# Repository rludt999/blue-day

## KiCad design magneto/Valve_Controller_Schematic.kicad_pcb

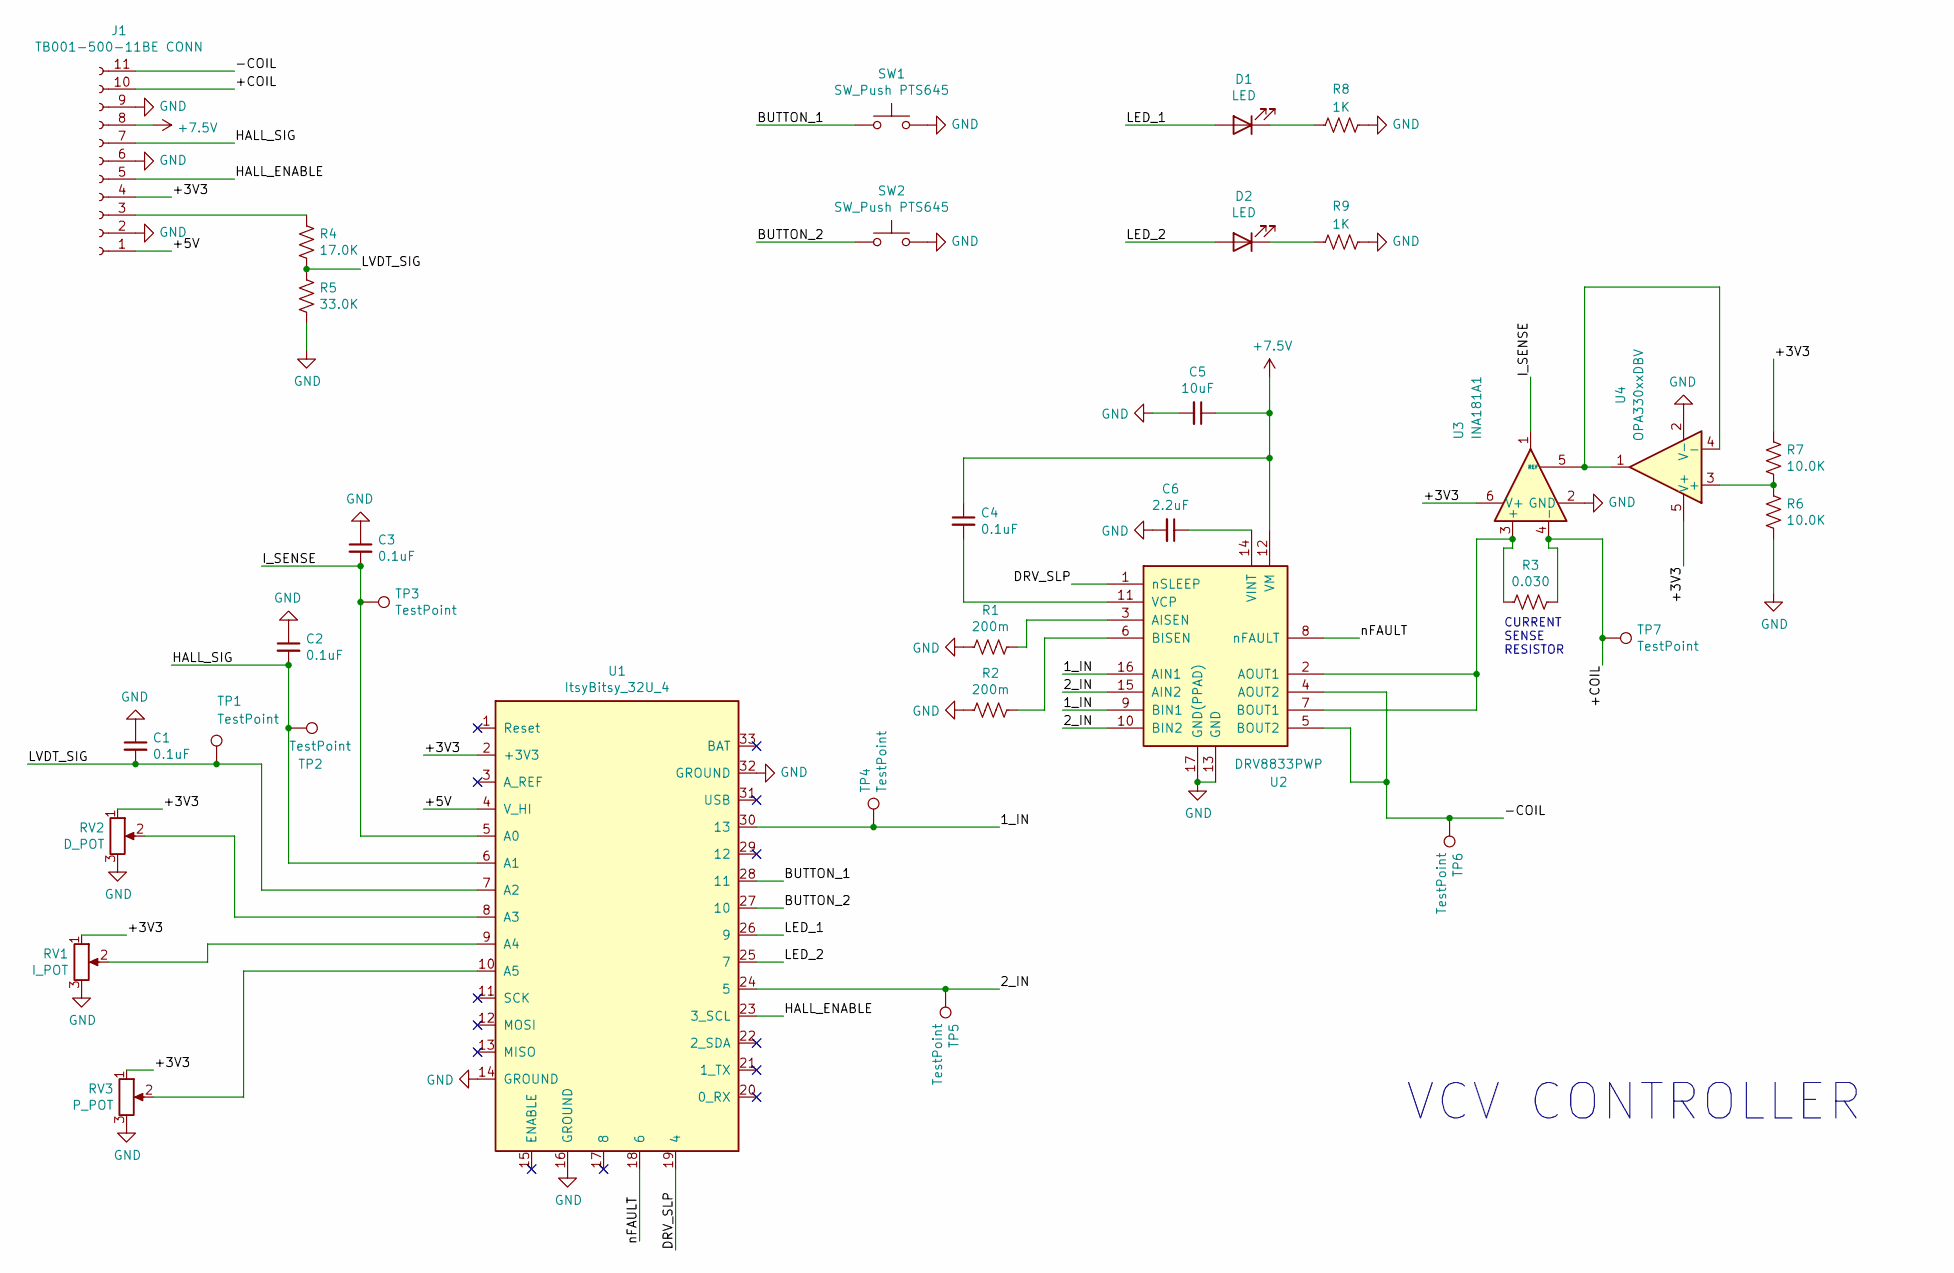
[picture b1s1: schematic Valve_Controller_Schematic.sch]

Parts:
C1, C2, C3, C4: 0.1uF; C_0805_2012Metric_Pad1.15x1.40mm_HandSolder
C5: 10uF; C_0805_2012Metric_Pad1.15x1.40mm_HandSolder
C6: 2.2uF; C_0805_2012Metric_Pad1.15x1.40mm_HandSolder
D1, D2: LED; LED_0805_2012Metric_Pad1.15x1.40mm_HandSolder
J1: TB001-500-11BE CONN; TB001-500-11BE
R1, R2: 200m; R_0805_2012Metric_Pad1.15x1.40mm_HandSolder
R3: 0.030; R_0805_2012Metric_Pad1.15x1.40mm_HandSolder
R4: 17.0K; R_0805_2012Metric_Pad1.15x1.40mm_HandSolder
R5: 33.0K; R_0805_2012Metric_Pad1.15x1.40mm_HandSolder
R6, R7: 10.0K; R_0805_2012Metric_Pad1.15x1.40mm_HandSolder
R8, R9: 1K; R_0805_2012Metric_Pad1.15x1.40mm_HandSolder
RV1: I_POT; Potentiometer_Bourns_3266Y_Vertical
RV2: D_POT; Potentiometer_Bourns_3266Y_Vertical
RV3: P_POT; Potentiometer_Bourns_3266Y_Vertical
SW1, SW2: SW_Push PTS645; SW_SPST_PTS645
TP1, TP2, TP3, TP4, TP5, TP6, TP7: TestPoint; TestPoint_Keystone_5000-5004_Miniature
U1: ItsyBitsy_32U_4
U2: DRV8833PWP; HTSSOP-16-1EP_4.4x5mm_P0.65mm_EP3.4x5mm_Mask2.46x2.31mm_The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
U3: INA181A1; SOT-23-6
U4: OPA330xxDBV; SOT-23-5

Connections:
+7.5V: C4.1, C5.1, J1.8, U2.12 (VM)
/1_IN: TP4.1, U1.30 (13), U2.9 (BIN1), U2.16 (AIN1)
/2_IN: TP5.1, U1.24 (5), U2.10 (BIN2), U2.15 (AIN2)
/+3V3: J1.4, R7.2, RV1.1, RV2.1, RV3.1, U1.2 (+3V3), U3.6 (V+), U4.5 (V+)
/+5V: J1.1, U1.4 (V_HI)
/+COIL: J1.10, R3.1, TP7.1, U3.4 (-)
/-COIL: J1.11, TP6.1, U2.4 (AOUT2), U2.5 (BOUT2)
/BUTTON_1: SW1.1, U1.28 (11)
/BUTTON_2: SW2.1, U1.27 (10)
/DRV_SLP: U1.19 (4), U2.1 (nSLEEP)
/HALL_ENABLE: J1.5, U1.23 (3_SCL)
/HALL_SIG: C2.2, J1.7, TP2.1, U1.6 (A1)
/I_SENSE: C3.2, TP3.1, U1.5 (A0), U3.1
/LED_1: D1.2 (A), U1.26 (9)
/LED_2: D2.2 (A), U1.25 (7)
/LVDT_SIG: C1.2, R4.2, R5.1, TP1.1, U1.7 (A2)
/nFAULT: U1.18 (6), U2.8 (nFAULT)
GND: C1.1, C2.1, C3.1, C5.2, C6.2, J1.2, J1.6, J1.9, R1.2, R2.2, R5.2, R6.1, R8.1, R9.1, RV1.3, RV2.3, RV3.3, SW1.2, SW2.2, U1.14 (GROUND), U1.16 (GROUND), U1.32 (GROUND), U2.13 (GND), U2.17 (GND(PPAD)), U3.2 (GND), U4.2 (V-)
unnamed: C4.2, U2.11 (VCP)
unnamed: C6.1, U2.14 (VINT)
unnamed: D1.1 (K), R8.2
unnamed: D2.1 (K), R9.2
unnamed: J1.3, R4.1
unnamed: R1.1, U2.3 (AISEN)
unnamed: R2.1, U2.6 (BISEN)
unnamed: R3.2, U2.2 (AOUT1), U2.7 (BOUT1), U3.3 (+)
unnamed: R6.2, R7.1, U4.3 (+)
unnamed: RV1.2, U1.9 (A4)
unnamed: RV2.2, U1.8 (A3)
unnamed: RV3.2, U1.10 (A5)
unnamed: U3.5 (REF), U4.1, U4.4 (-)

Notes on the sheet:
VCV CONTROLLER
CURRENT SENSE RESISTOR

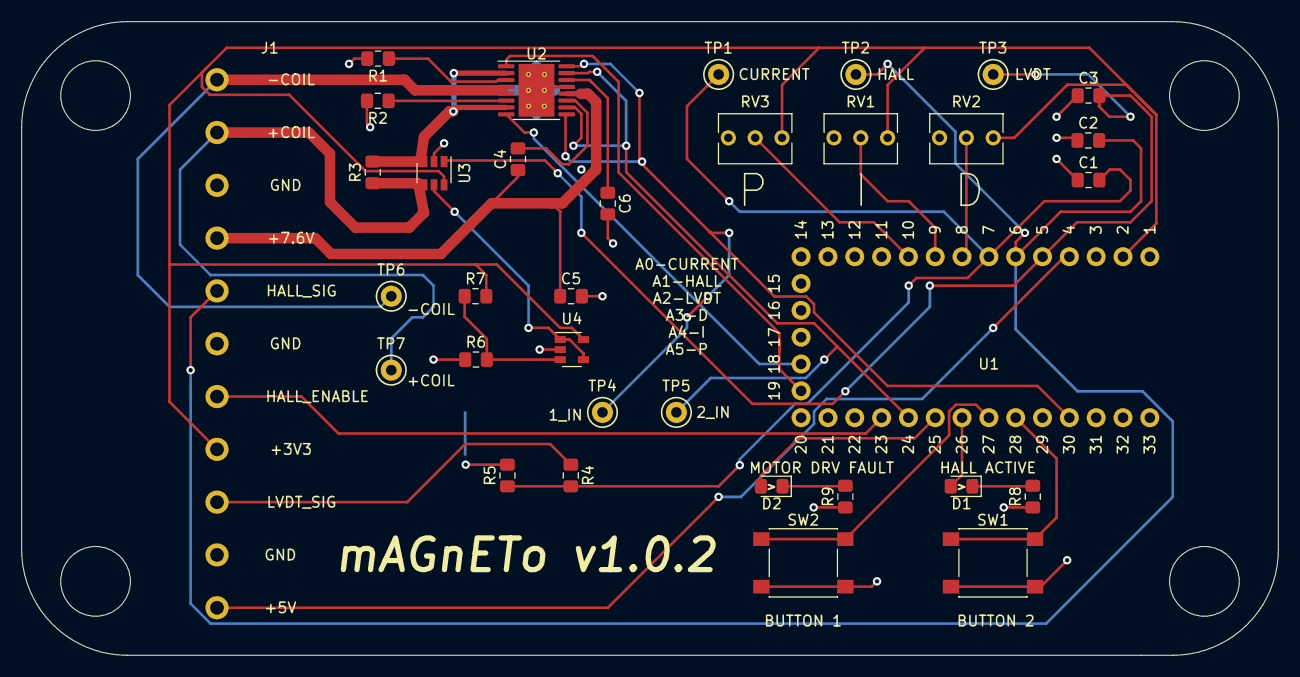
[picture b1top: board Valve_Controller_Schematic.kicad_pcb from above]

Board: 2 copper layers, 119.0 x 60.0 mm, 34 parts (0 on the bottom side), 31 nets.
